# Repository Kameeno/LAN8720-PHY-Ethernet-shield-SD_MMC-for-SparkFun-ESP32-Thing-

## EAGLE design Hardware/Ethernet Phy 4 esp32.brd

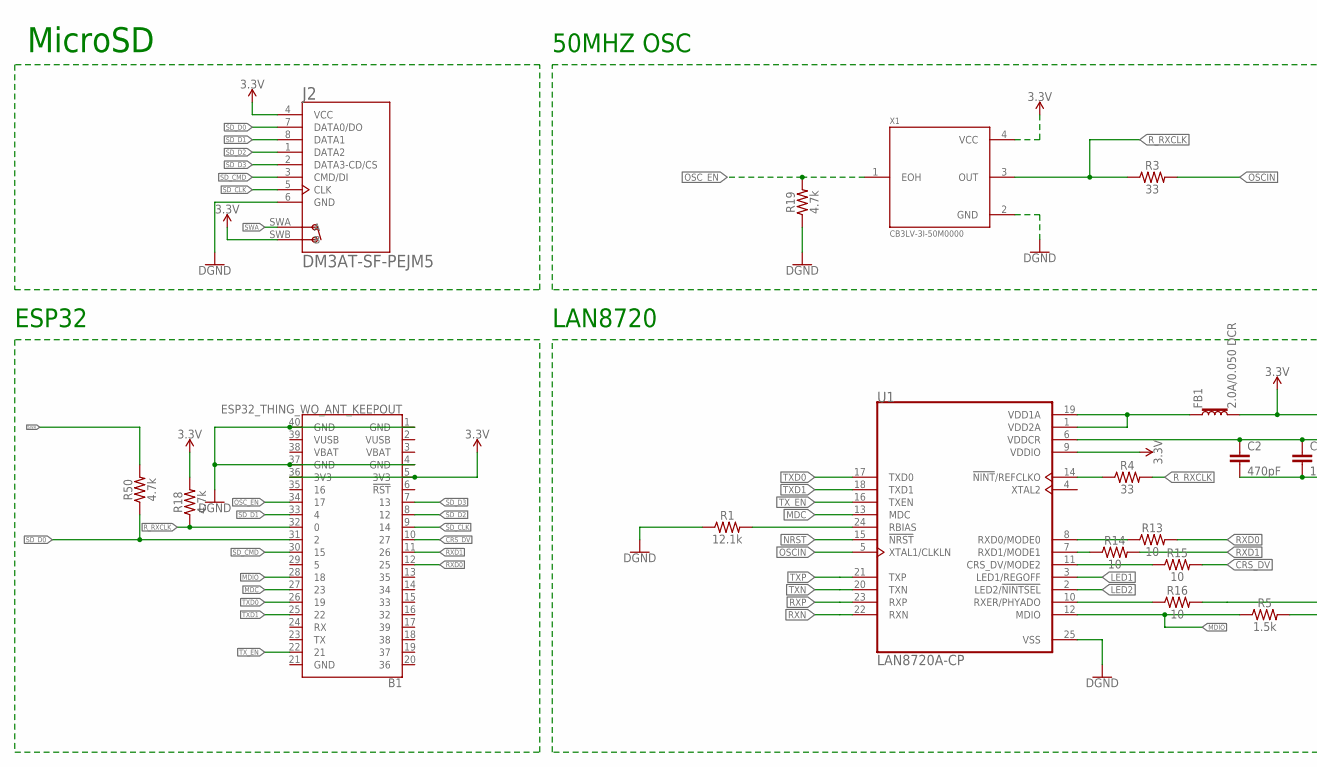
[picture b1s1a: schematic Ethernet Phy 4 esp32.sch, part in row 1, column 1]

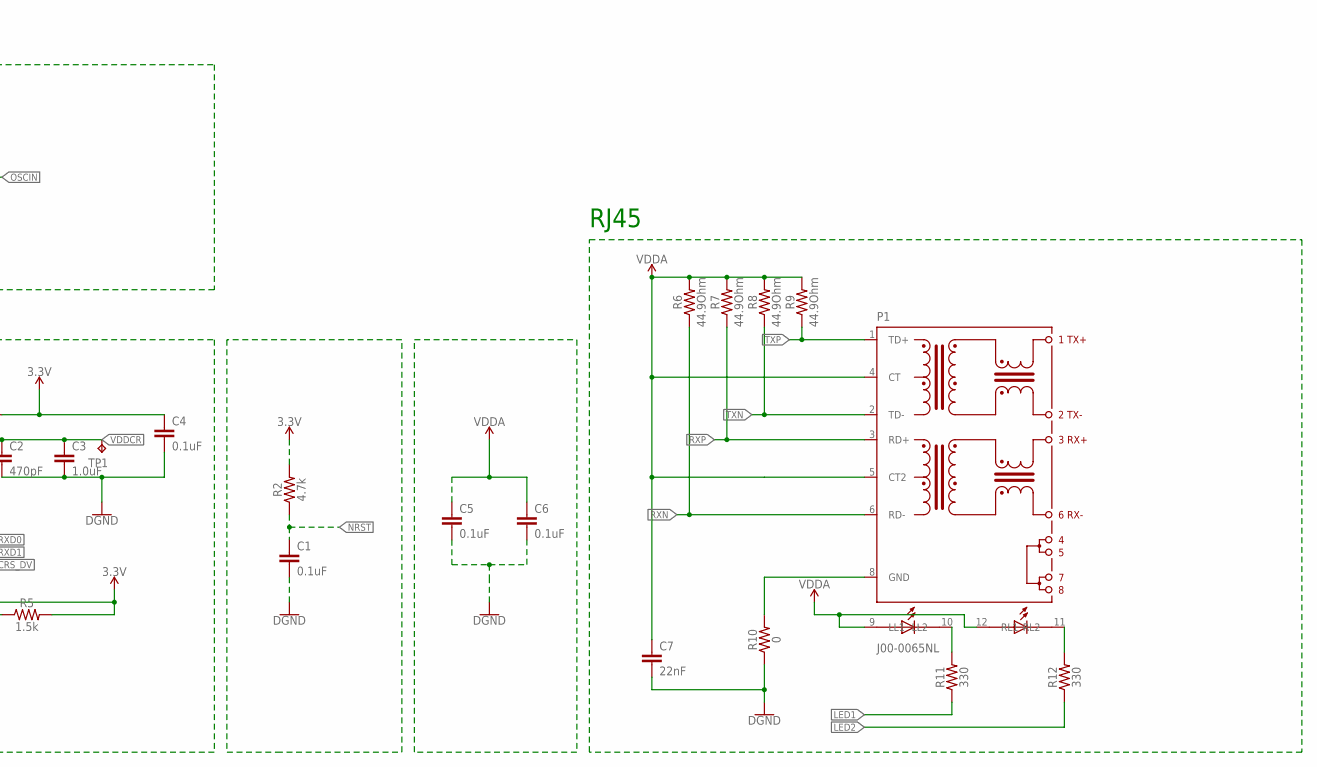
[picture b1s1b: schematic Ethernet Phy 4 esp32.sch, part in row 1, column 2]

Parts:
B1: ESP32_THING_WO_ANT_KEEPOUT; ESP32_THING_NO_ANT
C1, C4, C5, C6: 0.1uF; 0603
C2: 470pF; 0603
C3: 1.0uF; 0603
C7: 22nF; 0603
FB1: 2.0A/0.050 DCR; 0603
J2: DM3AT-SF-PEJM5; HRS_DM3AT-SF-PEJM5
P1: J00-0065NL; PULSE_J00-0065NL
R1: 12.1k; 0603
R2, R18, R19, R50: 4.7k; 0603
R3, R4: 33; 0603
R5: 1.5k; 0603
R6, R7, R8, R9: 44.9Ohm; 0603
R10: 0; 0603
R11, R12: 330; 0603
R13, R14, R15, R16: 10; 0603
TP1: TPB1,27; B1,27
U1: LAN8720A-CP; QFN50P400X400X100-25N
X1: CB3LV-3I-50M0000; OSCCC700X500X180-4N

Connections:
3.3V: B1.5 (3V3), B1.36 (3V3), C4.1, FB1.2, J2.4 (VCC), J2.SWB (B), R2.2, R5.2, R16.2, R18.2, U1.9 (VDDIO), X1.4 (VCC)
CRS_DV: B1.10 (27), R15.2
GND: B1.1 (GND), B1.4 (GND), B1.37 (GND), B1.40 (GND), C1.2, C2.2, C3.2, C4.2, C5.2, C6.2, C7.2, J2.6 (GND), R1.1, R10.1, R19.1, U1.25 (VSS), X1.2 (GND)
LED1: R11.1, U1.3 (LED1/REGOFF)
LED2: R12.1, U1.2 (LED2/!NINTSEL!)
MDC: B1.27 (23), U1.13 (MDC)
MDIO: B1.28 (18), R5.1, U1.12 (MDIO)
unnamed: R1.2, U1.24 (RBIAS)
unnamed: R4.1, U1.14 (!NINT!/REFCLKO)
unnamed: FB1.1, U1.1 (VDD2A), U1.19 (VDD1A)
unnamed: P1.10 (LL2), R11.2
unnamed: P1.8 (GND), R10.2
unnamed: P1.11 (RL2), R12.2
unnamed: R14.1, U1.7 (RXD1/MODE1)
unnamed: R13.1, U1.8 (RXD0/MODE0)
unnamed: R15.1, U1.11 (CRS_DV/MODE2)
unnamed: R16.1, U1.10 (RXER/PHYADO)
NRST: C1.1, R2.1, U1.15 (!NRST)
OSCIN: R3.2, U1.5 (XTAL1/CLKLN)
OSC_EN: B1.34 (17), R19.2, X1.1 (EOH)
RXD0: B1.12 (25), R13.2
RXD1: B1.11 (26), R14.2
RXN: P1.6 (RD-), R6.1, U1.22 (RXN)
RXP: P1.3 (RD+), R7.1, U1.23 (RXP)
R_RXCLK: B1.32 (0), R3.1, R4.2, R18.1, X1.3 (OUT)
SD_CLK: B1.9 (14), J2.5 (CLK)
SD_CMD: B1.30 (15), J2.3 (CMD/DI)
SD_D0: B1.31 (2), J2.7 (DATA0/DO), R50.1
SD_D1: B1.33 (4), J2.8 (DATA1)
SD_D2: B1.8 (12), J2.1 (DATA2)
SD_D3: B1.7 (13), J2.2 (DATA3-CD/CS)
SWA: J2.SWA (A), R50.2
TXD0: B1.26 (19), U1.17 (TXD0)
TXD1: B1.25 (22), U1.18 (TXD1)
TXN: P1.2 (TD-), R8.1, U1.20 (TXN)
TXP: P1.1 (TD+), R9.1, U1.21 (TXP)
TX_EN: B1.22 (21), U1.16 (TXEN)
VDDA: C5.1, C6.1, C7.1, P1.4 (CT), P1.5 (CT2), P1.9 (LL1), P1.12 (RL1), R6.2, R7.2, R8.2, R9.2
VDDCR: C2.1, C3.1, TP1.TP, U1.6 (VDDCR)

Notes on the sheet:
LAN8720
50MHZ OSC
RJ45
ESP32
MicroSD

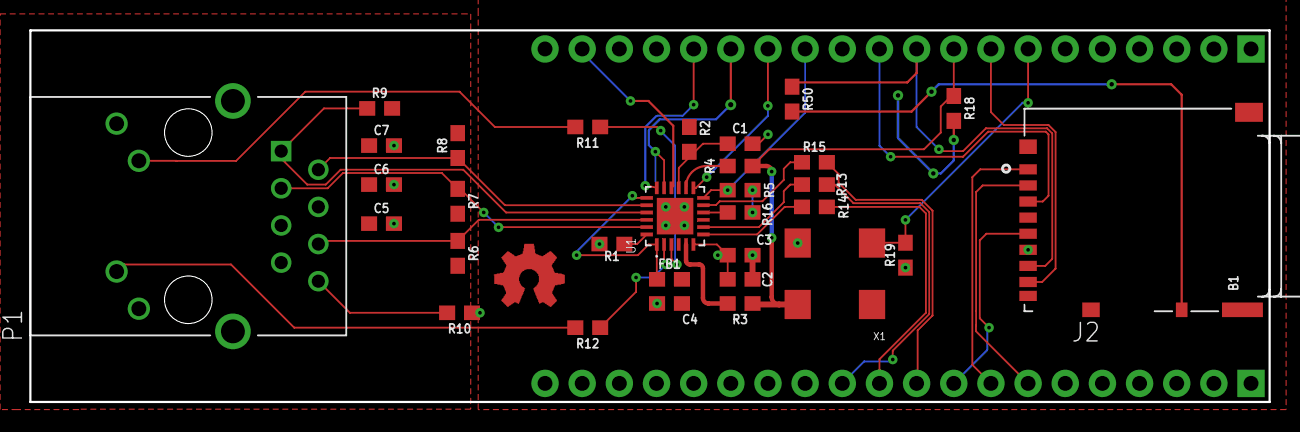
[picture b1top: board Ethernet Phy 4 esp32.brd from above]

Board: 2 copper layers, 84.7 x 25.4 mm, 33 parts (1 on the bottom side), 39 nets.

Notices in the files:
parts and their libraries:
SparkFun-Resistors: Licensing: Creative Commons ShareAlike 4.0 International - https://creativecommons.org/licenses/by-sa/4.0
